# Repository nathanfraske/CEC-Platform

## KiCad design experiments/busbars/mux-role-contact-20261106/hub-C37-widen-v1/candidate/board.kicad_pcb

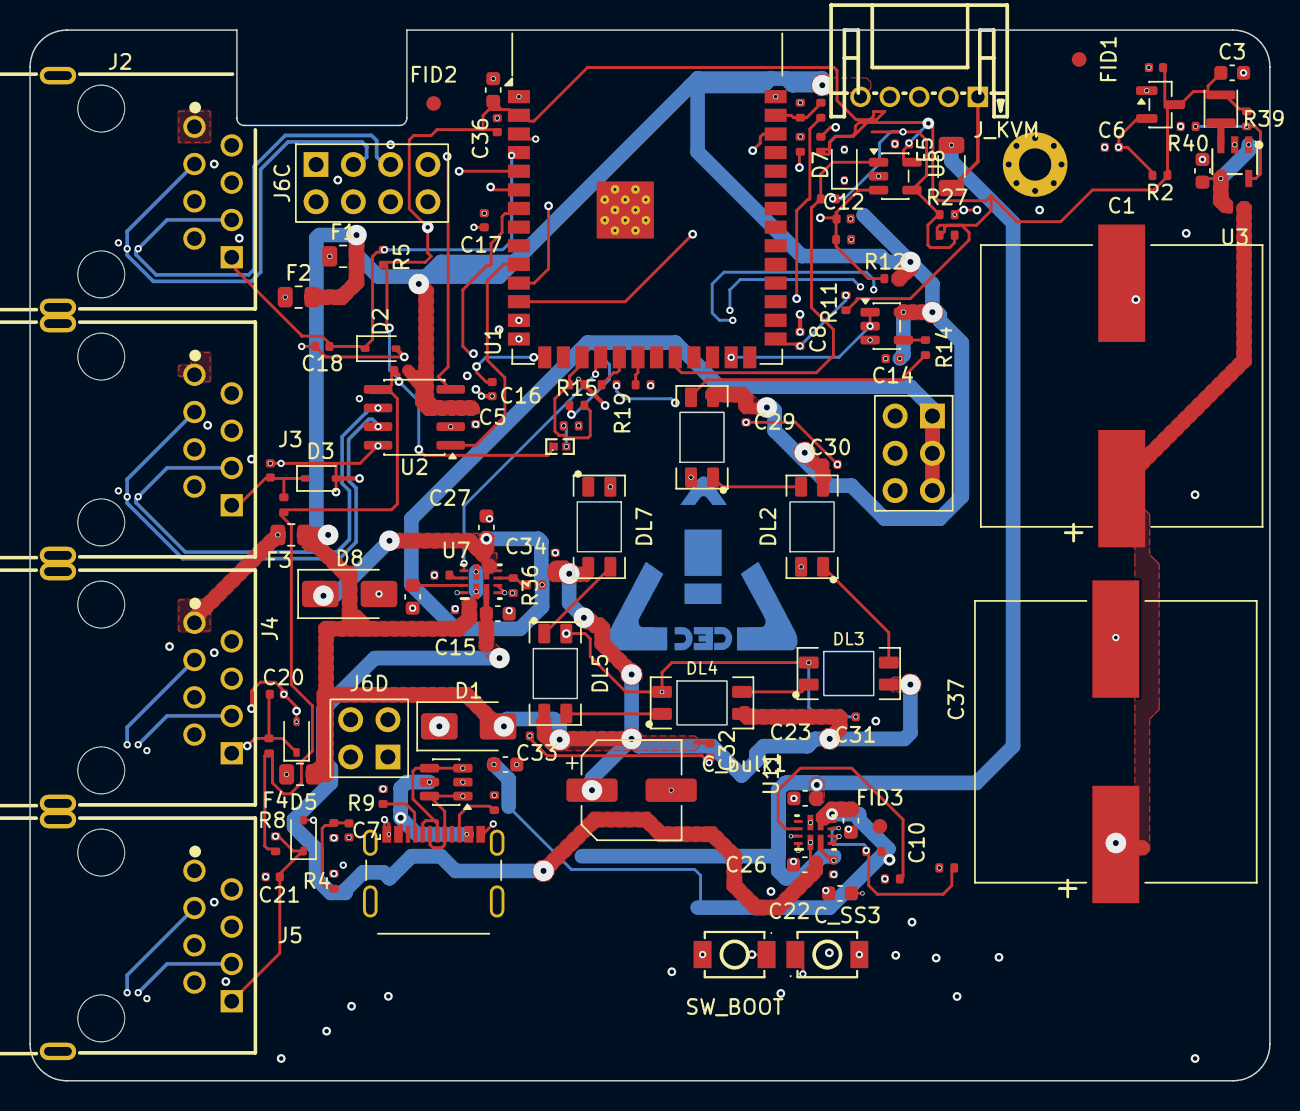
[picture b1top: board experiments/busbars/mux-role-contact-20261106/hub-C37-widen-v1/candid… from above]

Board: 6 copper layers, 84.5 x 71.6 mm, 117 parts (1 on the bottom side), 58 nets.

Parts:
C1, C37: 4700uF; CP_Elec_Lelon_VZH_18x16.5
C2, C3, C23: 10uF; C_0603_1608Metric
C4, C5, C6, C8, C13, C14, C15, C16, C17, C18, C19, C20, C21, C22, C29, C30, C31, C32, C33, C34, C35, C36: 100nF; C_0402_1005Metric
C7: 4n7; C_0402_1005Metric
C10, C25, C26, C27, C28: 1uF; C_0603_1608Metric
C11: 22uF; C_0603_1608Metric
C12: 10nF; C_0402_1005Metric
C_SS2, C_SS3: 2.2uF; C_0603_1608Metric
C_bulk1: 470uF; CP_Elec_6.3x7.7
D1: SS14; D_SMA
D2, D3, D4, D5, D7: PESD5V0S1BA; D_SOD-323
D6: USBLC6-2SC6; SOT-23-6
D8: SMAJ5.0A; D_SMA
DL1, DL2, DL3, DL4, DL5, DL7: SK6812MINI-E; LED_SK6812MINI-E_3.2x2.8mm_P1.5mm_ReverseMount
F1, F2, F3, F4: PTC 500mA; R_0805_2012Metric
F5: 1.1A/16V PTC; R_1206_3216Metric
FID1, FID2, FID3: Fiducial_1mm_Mask2mm
H1: M2 GND lug; MountingHole_2.2mm_M2_Pad_Via_Slim_6mm_Hardware
J2: PORT1; RJ45_FTP_Shielded_Horizontal
J3: PORT2; RJ45_FTP_Shielded_Horizontal
J4: PORT3; RJ45_FTP_Shielded_Horizontal
J5: PORT4; RJ45_FTP_Shielded_Horizontal
J6C: TO-24PIN-STACK-COMMS; PinSocket_2x04_P2.54mm_Vertical
J6D: TO-24PIN-STACK-ID; PinSocket_2x02_P2.54mm_Vertical
J6P: TO-24PIN-STACK-PWR; PinSocket_2x03_P2.54mm_Vertical
J_KVM: CEC_NANOKVM_AUX_5P; JST_PH_S5B-PH-K-S_1x05_P2.00mm_Horizontal
J_USB: USB-C; USB_C_Receptacle_GCT_USB4215-03-A
L1: 2.2uH; VLS252010HBX-2R2M-1
LOGO1: CEC_Logo_Copper
R2, R5, R6, R7, R8, R11, R16, R22, R24, R25, R36, R38: 10kΩ; R_0402_1005Metric
R3, R4: 60.4; R_0402_1005Metric
R9, R10: 5.1kΩ; R_0402_1005Metric
R12, R15, R21, R23: 47kΩ; R_0402_1005Metric
R13: 27kΩ; R_0402_1005Metric
R14: 330Ω; R_0402_1005Metric
R19, R20: 33Ω; R_0402_1005Metric
R26: 11.0kOhm; R_0402_1005Metric
R27: 10.0kOhm; R_0402_1005Metric
R28: 1MOhm; R_0402_1005Metric
R35, R37: 43.2kΩ; R_0402_1005Metric
R39: 453kΩ; R_0402_1005Metric
R40: 100kΩ; R_0402_1005Metric
RJ_HOLD: 0R (jumper); R_0402_1005Metric
R_ILIM2, R_ILIM3: 27kΩ; R_0402_1005Metric
SW_BOOT: SW_BOOT; TS-1088-AR02016
SW_RESET: SW_RST; TS-1088-AR02016
TH1: NTC 10k; NTC_0402_1005Metric
U1: ESP32-S3-WROOM-1; ESP32-S3-WROOM-1_NoAntKeepout
U2: TJA1051T/3; SOIC-8_3.9x4.9mm_P1.27mm
U3: TLV62569DBVR; SOT-23-5_L3.0-W1.7-P0.95-LS2.8-BL
U4: TPS3839K33; SOT-23
U6: SN74AHCT1G08; SOT-23-5
U7, U11: TPS2121RUXR; RUX0012A
U8: TLV7011DBVR; SOT-23-5

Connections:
+3V3: C3.1, C4.1, C11.1, C13.1, C17.1, C35.1, C36.1, L1.2, R2.1, R5.1, R6.1, R7.1, R8.1, R11.1, R23.1, R26.1, R39.1, TH1.1, U1.2, U2.5, U4.3, U8.5
+5VSB: C5.1, C14.1, C15.1, C29.1, C30.1, C31.1, C32.1, C33.1, C34.1, C35.2, C_bulk1.1, D1.2, DL1.4, DL2.4, DL3.4, DL4.4, DL5.4, DL7.4, F1.2, F2.2, F3.2, F4.2, R12.1, U2.3, U6.5, U7.1, U7.8
+5V_SYS: C27.1, D8.1, J6P.1, J6P.3, J6P.5, R15.1, R35.1, U7.6, U7.7
/5V_SYS_SENSE: R15.2, R16.1, U1.17
/AUX_UART_RX: R20.1, U1.20
/AUX_UART_TX: R19.1, U1.19
/BLACKOUT_SENSE: C12.1, R12.2, R13.1, U1.12, U8.3
/CAN + FOUR MODULE PORTS + STACK/CAN_H: J2.3, J3.3, J4.3, J5.3, J6C.3, R3.1, U2.7
/CAN + FOUR MODULE PORTS + STACK/CAN_L: J2.6, J3.6, J4.6, J5.6, J6C.5, R4.2, U2.6
/CAN + FOUR MODULE PORTS + STACK/CAN_MID: C7.1, R3.2, R4.1
/CAN + FOUR MODULE PORTS + STACK/VCC_P1: F1.1, J2.1
/CAN + FOUR MODULE PORTS + STACK/VCC_P2: F2.1, J3.1
/CAN + FOUR MODULE PORTS + STACK/VCC_P3: F3.1, J4.1
/CAN + FOUR MODULE PORTS + STACK/VCC_P4: F4.1, J5.1
/CAN_RX: U1.11, U2.4
/CAN_TX: U1.10, U2.1
/DETECT1: C18.1, D2.1, J2.8, J6D.1, R5.2, U1.4
/DETECT2: C19.1, D3.1, J3.8, R6.2, U1.5
/DETECT3: C20.1, D4.1, J4.8, R7.2, U1.6
/DETECT4: C21.1, D5.1, J5.8, R8.2, U1.7
/HOLD-UP + 3V3 REGULATOR/+5V_HOLD: C1.1, C37.1, D1.1, RJ_HOLD.1
/HOLD-UP + 3V3 REGULATOR/BUCK_FB_3V3: R39.2, R40.1, U3.5
/HOLD-UP + 3V3 REGULATOR/BUCK_SW_3V3: L1.1, U3.3
/HOLD-UP + 3V3 REGULATOR/COMP_THRESH: R26.2, R27.1, R28.2, U8.4
/HOLD-UP + 3V3 REGULATOR/LOGIC_REG_IN: C2.1, RJ_HOLD.2, U3.1, U3.4
/HUB_3V3_SENSE: R23.2, R24.1, U1.38
/KVM AUXILIARY + RAIL SENSING/AUX_RXC: J_KVM.4, R20.2
/KVM AUXILIARY + RAIL SENSING/AUX_TXC: J_KVM.3, R19.2
/KVM AUXILIARY + RAIL SENSING/KVM_3V3_REF: D7.1, J_KVM.5, R21.1
/KVM AUXILIARY + RAIL SENSING/KVM_5V_RAW: F5.1, J_KVM.1
/KVM_3V3_SENSE: R21.2, R22.1, U1.39
/KVM_5V_IN: C22.1, C23.1, F5.2, U11.2
/LED_DATA: U1.25, U6.1, U6.2
/MCU + USB SERVICE PORT/EN: C6.2, R2.2, SW_RESET.2, U1.3, U4.2
/MCU + USB SERVICE PORT/GPIO0: C8.1, R11.2, SW_BOOT.2, U1.27
/MCU + USB SERVICE PORT/USB_CC1: J_USB.A5, R9.1
/MCU + USB SERVICE PORT/USB_CC2: J_USB.B5, R10.1
/MCU + USB SERVICE PORT/USB_D_N: D6.3, D6.4, J_USB.A7, J_USB.B7, U1.13
/MCU + USB SERVICE PORT/USB_D_P: D6.1, D6.6, J_USB.A6, J_USB.B6, U1.14
/POWER INPUT + SOURCE SELECTION/PSU_5V_KVM: C26.1, C28.1, U7.2, U11.1, U11.8
/POWER INPUT + SOURCE SELECTION/U7_ILM: R_ILIM2.1, U7.10
/POWER INPUT + SOURCE SELECTION/U7_OV1: R35.2, R36.1, U7.5
/POWER INPUT + SOURCE SELECTION/U7_SS: C_SS2.1, U7.11
/POWER INPUT + SOURCE SELECTION/U11_ILM: R_ILIM3.1, U11.10
/POWER INPUT + SOURCE SELECTION/U11_OV1: R37.2, R38.1, U11.5
/POWER INPUT + SOURCE SELECTION/U11_SS: C_SS3.2, U11.11
/PWR_FAIL_INT: R28.1, U1.22, U8.1
/PWR_SOURCE_STATUS: U1.18, U7.9
/STATUS LED CHAIN/Net-(U6-Y): R14.1, U6.4
/TEMP_HUB: C16.1, R25.1, TH1.2, U1.15
/USB_VBUS: C10.1, C25.1, D6.5, J_USB.A4, J_USB.A9, J_USB.B4, J_USB.B9, R37.1, U11.6, U11.7
GND: C1.2, C2.2, C3.2, C4.2, C5.2, C6.1, C7.2, C8.2, C10.2, C11.2, C12.2, C13.2, C14.2, C15.2, C16.2, C17.2, C18.2, C19.2, C20.2, C21.2, C22.2, C23.2, C25.2, C26.2, C27.2, C28.2, C29.2, C30.2, C31.2, C32.2, C33.2, C34.2, C36.2, C37.2, C_SS2.2, C_SS3.1, C_bulk1.2, D2.2, D3.2, D4.2, D5.2, D6.2, D7.2, D8.2, DL1.2, DL2.2, DL3.2, DL4.2, DL5.2, DL7.2, H1.1, J2.2, J2.SH1, J2.SH2, J3.2, J3.SH1, J3.SH2, J4.2, J4.SH1, J4.SH2, J5.2, J5.SH1, J5.SH2, J6C.1, J6C.2, J6C.7, J6C.8, J6D.2, J6D.4, J6P.2, J6P.4, J6P.6, J_KVM.2, J_USB.A1, J_USB.A12, J_USB.B1, J_USB.B12, J_USB.S1, R9.2, R10.2, R13.2, R16.2, R22.2, R24.2, R25.2, R27.2, R36.2, R38.2, R40.2, R_ILIM2.2, R_ILIM3.2, SW_BOOT.1, SW_RESET.1, U1.1, U1.40, U1.41, U2.2, U2.8, U3.2, U4.1, U6.3, U7.3, U7.4, U7.12, U8.2, U11.3, U11.4, U11.12
unnamed: DL1.3, R14.2
unnamed: DL1.1, DL2.3
unnamed: DL2.1, DL3.3
unnamed: DL3.1, DL4.3
unnamed: DL4.1, DL5.3
unnamed: DL5.1, DL7.3

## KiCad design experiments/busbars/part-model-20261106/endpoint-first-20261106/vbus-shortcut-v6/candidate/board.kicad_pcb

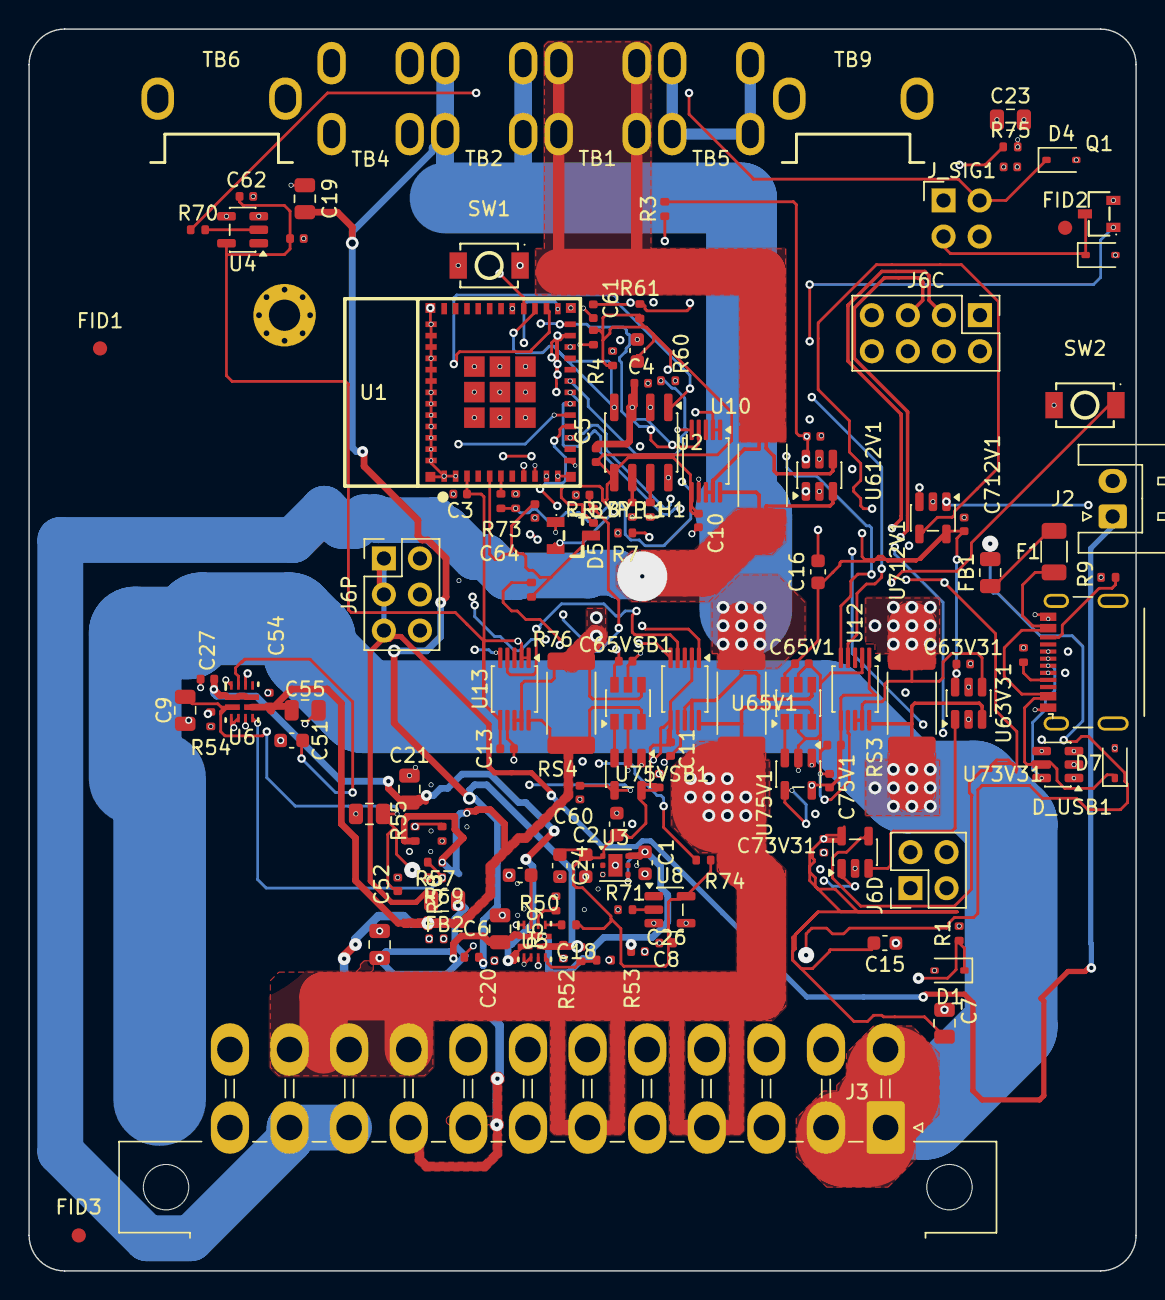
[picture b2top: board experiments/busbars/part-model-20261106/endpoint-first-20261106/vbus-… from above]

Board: 6 copper layers, 78.0 x 87.5 mm, 129 parts (0 on the bottom side), 63 nets.

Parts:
C1, C2, C14, C15, C16, C17, C24: 1uF; C_0603_1608Metric
C3, C4, C5, C8, C10, C11, C12, C13, C18, C20, C22, C26, C27, C28, C52, C54, C60, C61, C62, C63, C63V31, C64, C65V1, C65VSB1, C73V31, C75V1, C75VSB1, C612V1, C712V1: 100nF; C_0402_1005Metric
C6, C7, C9, C19, C21, C23, C53, C55: 10uF; C_0805_2012Metric
C25: 22uF; C_0805_2012Metric
C50: 2u2; C_0603_1608Metric
C51: 2.2uF; C_0603_1608Metric
D1, D3, D4, D7: PESD5V0S1BA; D_SOD-323
D5: BAT54S; SOT-23-3_L2.9-W1.3-P1.90-LS2.4-TL
D_USB1: USBLC6-2SC6; SOT-23-6
F1: 750mA/16V PTC; R_1206_3216Metric
FB1: 600R@100MHz FB (MPZ2012S601AT000); C_0805_2012Metric
FB2: 0R (FB position, populate on EMC evidence); C_0805_2012Metric
FID1, FID2, FID3: Fiducial_1mm_Mask2mm
H1: M2 GND lug; MountingHole_2.2mm_M2_Pad_Via_Slim_6mm_Hardware
J2: TO-HUB-PWR; JST_XH_S2B-XH-A_1x02_P2.50mm_Horizontal
J3: ATX-24 PSU; Molex_Mini-Fit_Jr_5569-24A1_2x12_P4.20mm_Horizontal
J5: USB-C 2.0; USB_C_Receptacle_GCT_USB4215-03-A
J6C: TO-HUB-STACK-COMMS; PinHeader_2x04_P2.54mm_Vertical
J6D: TO-HUB-STACK-ID; PinHeader_2x02_P2.54mm_Vertical
J6P: TO-HUB-STACK-PWR; PinHeader_2x03_P2.54mm_Vertical
J_SIG1: SSQ-102-03-G-D; Samtec_SSQ-102-03-G-D_2x02_P2.54mm_Vertical
Q1: AO3400A; SOT-23-3_L2.9-W1.3-P1.90-LS2.4-BR
R1, R3, R4: 2.2kΩ; R_0402_1005Metric
R2, R10, R51, R56, R60, R61, R69, R76: 10kΩ; R_0402_1005Metric
R7, R52, R54, R57, R73, R75: 100kΩ; R_0402_1005Metric
R8, R9: 5.1kΩ; R_0402_1005Metric
R50: 20kΩ; R_0402_1005Metric
R53, R58: 33kΩ; R_0402_1005Metric
R55, R59: 43.2kΩ; R_0402_1005Metric
R70, R71: 1kΩ; R_0402_1005Metric
R72: 100Ω; R_0402_1005Metric
R74: 15kΩ; R_0402_1005Metric
RS1, RS2, RS3: 2mΩ; R_2512_6332Metric
RS4: R025; R_2512_6332Metric
R_BYP_H1: 0Ω; R_0402_1005Metric
R_BYP_L1: 0Ω; R_0402_1005Metric
SW1: BOOT; TS-1088-AR02016
SW2: RESET; TS-1088-AR02016
TB1, TB2, TB4, TB5: XFCN T34069; XFCN_T34069_THT_M3_40A
TB6, TB9: TTR32100127-0600; XFCN_TTR32100127-0600_THT_M3_60A
U1: ESP32-C6-MINI-1-N4; ESP32-C6-MINI-1
U2: TJA1051T/3; SOIC-8_3.9x4.9mm_P1.27mm
U3: TLV75533PDRVR; WSON-6-1EP_2x2mm_P0.65mm_EP1x1.6mm
U4, U8: 74LVC1G17; SOT-23-5
U5, U6: TPS2121RUXR; RUX0012A
U10, U11, U12, U13: INA238; VSSOP-10_3x3mm_P0.5mm
U63V31, U612V1: INA181A2IDBVR; SOT-23-6
U65V1, U65VSB1: INA181A2IDBVR; SOT-23-6_TI_DBV0006A
U73V31, U75V1, U75VSB1, U712V1: TLV7011DBVR; SOT-23-5

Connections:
+3V3: C2.1, C3.1, C7.1, C8.1, C10.1, C11.1, C12.1, C13.1, C14.1, C15.1, C16.1, C17.1, C24.1, C28.1, C62.1, C63.1, C63V31.1, C65V1.1, C65VSB1.1, C73V31.1, C75V1.1, C75VSB1.1, C612V1.1, C712V1.1, D5.2, R2.1, R3.2, R4.2, R10.1, R51.2, R61.1, R74.1, U1.3, U2.5, U3.1, U4.5, U8.5, U10.6, U11.2, U11.6, U12.1, U12.6, U13.1, U13.2, U13.6, U63V31.6, U65V1.6, U65VSB1.6, U73V31.5, U75V1.5, U75VSB1.5, U612V1.6, U712V1.5
+5VSB: C54.1, C55.1, J3.9, R55.1, R57.1, RS4.1, U6.7, U13.10, U65VSB1.3
+5V_MAIN: C18.1, C19.1, R52.1, R59.1, RS2.2, TB2.1, U5.7, U11.8, U11.9, U65V1.4
+5V_SYS: C1.1, C4.1, C6.1, C25.1, C26.1, C28.2, FB2.1, U2.3, U3.4, U3.6, U5.1, U5.8
/3V3 REGULATOR + MCU/EN: C5.1, R2.2, SW2.2, U1.8
/3V3 REGULATOR + MCU/IO8_STRAP: R10.2, U1.22
/5V SOURCE MUX + USB SERVICE INGRESS/5VSB_MUX: C20.1, C21.1, C27.1, U5.2, U6.1, U6.8
/5V SOURCE MUX + USB SERVICE INGRESS/ILIM: R50.1, U5.10
/5V SOURCE MUX + USB SERVICE INGRESS/MUX_ST: R51.1, U5.9
/5V SOURCE MUX + USB SERVICE INGRESS/PR1: R52.2, R53.1, U5.6
/5V SOURCE MUX + USB SERVICE INGRESS/SS: C50.1, U5.11
/5V SOURCE MUX + USB SERVICE INGRESS/U5_OV1: R59.2, R69.1, U5.5
/5V SOURCE MUX + USB SERVICE INGRESS/U6_ILM: R54.1, U6.10
/5V SOURCE MUX + USB SERVICE INGRESS/U6_OV1: R55.2, R56.1, U6.5
/5V SOURCE MUX + USB SERVICE INGRESS/U6_PR1: R57.2, R58.1, U6.6
/5V SOURCE MUX + USB SERVICE INGRESS/U6_SS: C51.1, U6.11
/5V SOURCE MUX + USB SERVICE INGRESS/USB_CC1: J5.A5, R8.1
/5V SOURCE MUX + USB SERVICE INGRESS/USB_CC2: J5.B5, R9.1
/5V SOURCE MUX + USB SERVICE INGRESS/VBUS: C9.1, C52.1, C53.1, FB1.2, U6.2
/5V SOURCE MUX + USB SERVICE INGRESS/VBUS_F: F1.2, FB1.1
/5V SOURCE MUX + USB SERVICE INGRESS/VBUS_RAW: D7.1, D_USB1.5, F1.1, J5.A4, J5.A9, J5.B4, J5.B9
/ATX INTERPOSER + CONTROL SIGNALS/ATX_NEG12V: C22.1, C23.1, J3.14, J_SIG1.1, R75.2
/ATX INTERPOSER + CONTROL SIGNALS/ATX_PSON: D3.1, J3.16, J_SIG1.2, Q1.3, R71.1
/ATX INTERPOSER + CONTROL SIGNALS/ATX_PWROK: D4.1, J3.8, J_SIG1.3, R70.1
/ATX INTERPOSER + CONTROL SIGNALS/NEG12V_DIV: R74.2, R75.1, R76.1
/ATX INTERPOSER + CONTROL SIGNALS/PSON_BUF: R71.2, U8.2
/ATX INTERPOSER + CONTROL SIGNALS/PSON_GATE: Q1.1, R72.2, R73.1
/ATX INTERPOSER + CONTROL SIGNALS/PWROK_BUF: R70.2, U4.2
/CAN_RX: U1.27, U2.4
/CAN_TX: U1.26, U2.1
/DET3V3: U1.15, U73V31.1
/DET5V: U1.29, U75V1.1
/DET5VSB: U1.16, U75VSB1.1
/DET12V: U1.28, U712V1.1
/DETECT_SENSE: R7.1, U1.12
/FOUR-RAIL PRECISION + FAST SENSING/DETAMP3V3: U63V31.1, U73V31.3
/FOUR-RAIL PRECISION + FAST SENSING/DETAMP5V: U65V1.1, U75V1.3
/FOUR-RAIL PRECISION + FAST SENSING/DETAMP5VSB: U65VSB1.1, U75VSB1.3
/FOUR-RAIL PRECISION + FAST SENSING/DETAMP12V: U612V1.1, U712V1.3
/FOUR-RAIL PRECISION + FAST SENSING/THRESH: C60.1, R60.2, U73V31.4, U75V1.4, U75VSB1.4, U712V1.4
/GPIO0: C61.1, R61.2, SW1.2, U1.23
/HUB LINK + CAN + STACK/+5V_SYS_PORT: FB2.2, J2.1, J6P.1, J6P.3, J6P.5
/HUB LINK + CAN + STACK/CAN_H: R_BYP_H1.2, U2.7
/HUB LINK + CAN + STACK/CAN_H_BUS: J6C.3, R_BYP_H1.1
/HUB LINK + CAN + STACK/CAN_L: R_BYP_L1.2, U2.6
/HUB LINK + CAN + STACK/CAN_L_BUS: J6C.5, R_BYP_L1.1
/HUB LINK + CAN + STACK/DETECT: D1.1, J6D.1, R1.1, R7.2
/I2C_SCL: R4.1, U1.25, U10.5, U11.5, U12.5, U13.5
/I2C_SDA: R3.1, U1.24, U10.4, U11.4, U12.4, U13.4
/NEG12V_ADC: C64.1, D5.3, R76.2, U1.5
/PSON_DRIVE: R72.1, U1.6
/PSON_SENSE: U1.10, U8.4
/PWROK_SENSE: U1.9, U4.4
/SENSE3V3_HI: J3.1, J3.2, J3.12, J3.13, RS3.1, U12.10, U63V31.3
/SENSE3V3_LO: RS3.2, TB4.1, U12.8, U12.9, U63V31.4
/SENSE5VSB_LO: RS4.2, TB5.1, U13.8, U13.9, U65VSB1.4
/SENSE5V_HI: J3.4, J3.6, J3.21, J3.22, J3.23, RS2.1, U11.10, U65V1.3
/SENSE12V_HI: J3.10, J3.11, RS1.1, U10.10, U612V1.3
/SENSE12V_LO: RS1.2, TB1.1, U10.8, U10.9, U612V1.4
/THRESH_PWM: R60.1, U1.19
/USB_D_N: D_USB1.3, D_USB1.4, J5.A7, J5.B7, U1.17
/USB_D_P: D_USB1.1, D_USB1.6, J5.A6, J5.B6, U1.18
GND: C1.2, C2.2, C3.2, C4.2, C5.2, C6.2, C7.2, C8.2, C9.2, C10.2, C11.2, C12.2, C13.2, C14.2, C15.2, C16.2, C17.2, C18.2, C19.2, C20.2, C21.2, C22.2, C23.2, C24.2, C25.2, C26.2, C27.2, C50.2, C51.2, C52.2, C53.2, C54.2, C55.2, C60.2, C61.2, C62.2, C63.2, C63V31.2, C64.2, C65V1.2, C65VSB1.2, C73V31.2, C75V1.2, C75VSB1.2, C612V1.2, C712V1.2, D1.2, D3.2, D4.2, D5.1, D7.2, D_USB1.2, H1.1, J2.2, J3.3, J3.5, J3.7, J3.15, J3.17, J3.18, J3.19, J3.24, J5.A1, J5.A12, J5.B1, J5.B12, J5.S1, J6C.1, J6C.2, J6C.7, J6C.8, J6D.2, J6D.4, J6P.2, J6P.4, J6P.6, J_SIG1.4, Q1.2, R1.2, R8.2, R9.2, R50.2, R53.2, R54.2, R56.2, R58.2, R69.2, R73.2, SW1.1, SW2.1, TB6.1, TB9.1, U1.1, U1.2, U1.11, U1.14, U1.36, U1.37, U1.38, U1.39, U1.40, U1.41, U1.42, U1.43, U1.44, U1.45, U1.46, U1.47, U1.48, U1.49, U1.50, U1.51, U1.52, U1.53, U2.2, U2.8, U3.3, U3.7, U4.3, U5.3, U5.4, U5.12, U6.3, U6.4, U6.12, U8.3, U10.1, U10.2, U10.7, U11.1, U11.7, U12.2, U12.7, U13.7, U63V31.2, U63V31.5, U65V1.2, U65V1.5, U65VSB1.2, U65VSB1.5, U73V31.2, U75V1.2, U75VSB1.2, U612V1.2, U612V1.5, U712V1.2
